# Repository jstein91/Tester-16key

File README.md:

# Tester 16key
 16 key Micropad design

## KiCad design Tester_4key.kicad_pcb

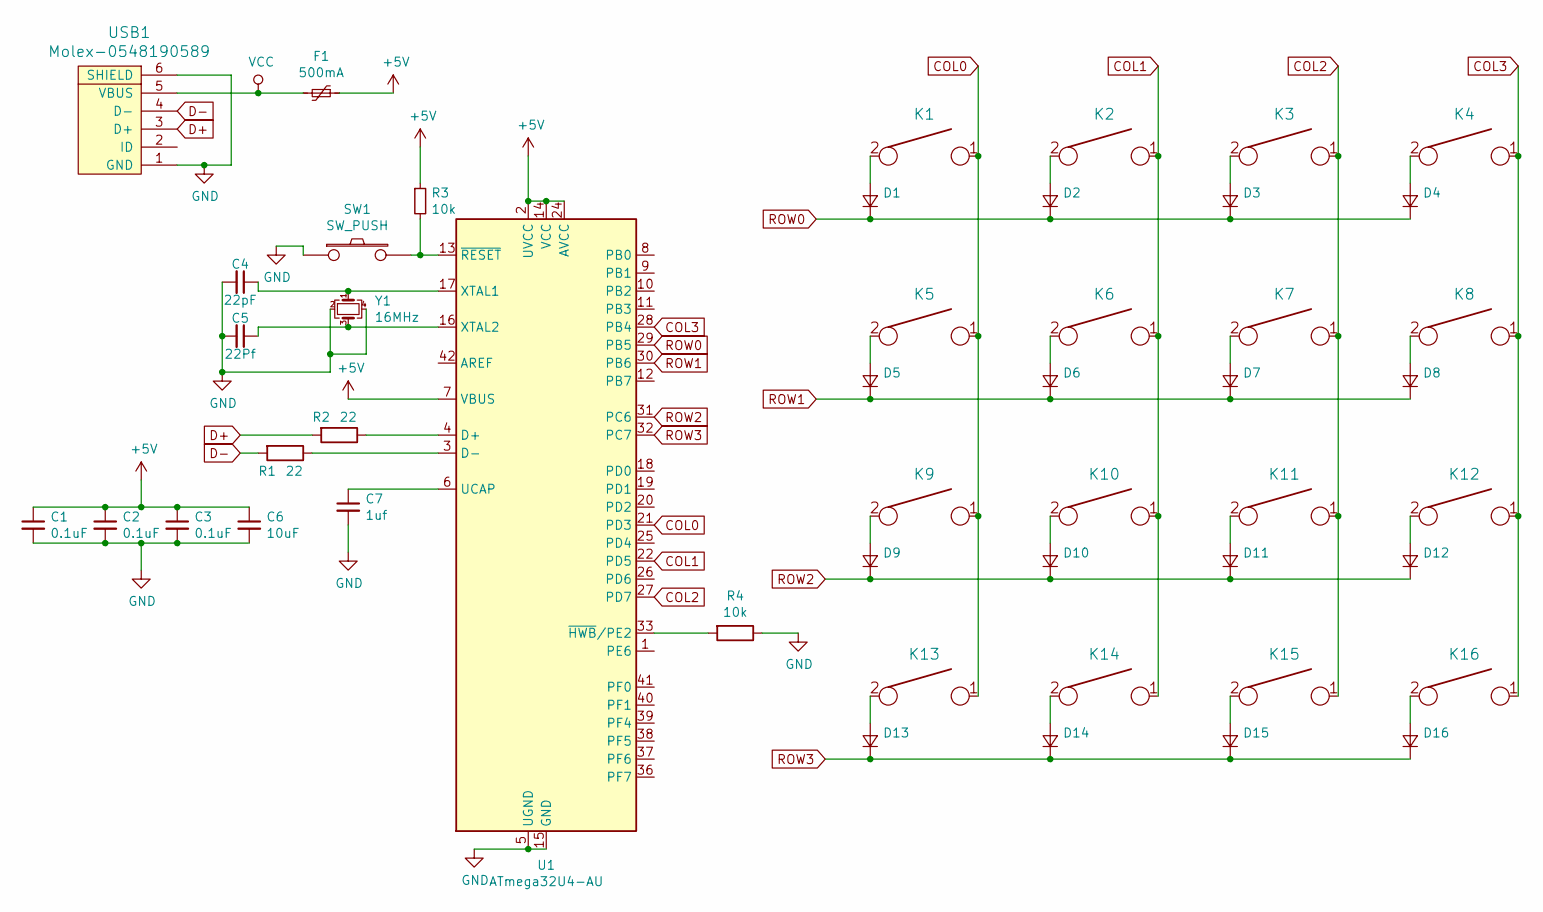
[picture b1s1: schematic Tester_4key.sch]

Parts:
C1, C2, C3: 0.1uF; C_0805_2012Metric_Pad1.15x1.40mm_HandSolder
C4: 22pF; C_0805_2012Metric_Pad1.15x1.40mm_HandSolder
C5: 22Pf; C_0805_2012Metric_Pad1.15x1.40mm_HandSolder
C6: 10uF; C_0805_2012Metric_Pad1.15x1.40mm_HandSolder
C7: 1uf; C_0805_2012Metric_Pad1.15x1.40mm_HandSolder
D1, D2, D3, D4, D5, D6, D7, D8, D9, D10, D11, D12, D13, D14, D15, D16: D_SOD123_axial
F1: 500mA; Fuse_1206_3216Metric_Pad1.42x1.75mm_HandSolder
K1, K2, K3, K4, K5, K6, K7, K8, K9, K10, K11, K12, K13, K14, K15, K16: KEYSW; Mx_Alps_100
R1, R2: 22; R_0805_2012Metric_Pad1.15x1.40mm_HandSolder
R3, R4: 10k; R_0805_2012Metric_Pad1.15x1.40mm_HandSolder
SW1: SW_PUSH; SKQG-1155865
U1: ATmega32U4-AU; TQFP-44_10x10mm_P0.8mm
USB1: Molex-0548190589
Y1: 16MHz; Crystal_SMD_3225-4Pin_3.2x2.5mm_HandSoldering

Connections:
+5V: C1.1, C2.1, C3.1, C6.1, F1.1, R3.1, U1.2 (UVCC), U1.7 (VBUS), U1.14 (VCC), U1.24 (AVCC), U1.34 (VCC), U1.44 (AVCC)
COL0: K1.1, K5.1, K9.1, K13.1, U1.21 (PD3)
COL1: K2.1, K6.1, K10.1, K14.1, U1.22 (PD5)
COL2: K3.1, K7.1, K11.1, K15.1, U1.27 (PD7)
COL3: K4.1, K8.1, K12.1, K16.1, U1.28 (PB4)
D+: R2.2, USB1.3 (D+)
D-: R1.2, USB1.4 (D-)
GND: C1.2, C2.2, C3.2, C4.2, C5.2, C6.2, C7.2, R4.1, SW1.1, U1.5 (UGND), U1.15 (GND), U1.23 (GND), U1.35 (GND), U1.43 (GND), USB1.1 (GND), USB1.6 (SHIELD), Y1.2, Y1.4
unnamed: C4.1, U1.17 (XTAL1), Y1.1
unnamed: C5.1, U1.16 (XTAL2), Y1.3
unnamed: C7.1, U1.6 (UCAP)
unnamed: D1.2 (A), K1.2
unnamed: D2.2 (A), K2.2
unnamed: D3.2 (A), K3.2
unnamed: D4.2 (A), K4.2
unnamed: D5.2 (A), K5.2
unnamed: D6.2 (A), K6.2
unnamed: D7.2 (A), K7.2
unnamed: D8.2 (A), K8.2
unnamed: D9.2 (A), K9.2
unnamed: D10.2 (A), K10.2
unnamed: D11.2 (A), K11.2
unnamed: D12.2 (A), K12.2
unnamed: D13.2 (A), K13.2
unnamed: D14.2 (A), K14.2
unnamed: D15.2 (A), K15.2
unnamed: D16.2 (A), K16.2
unnamed: R1.1, U1.3 (D-)
unnamed: R2.1, U1.4 (D+)
unnamed: R3.2, SW1.2, U1.13 (~RESET)
unnamed: R4.2, U1.33 (~HWB~/PE2)
ROW0: D1.1 (K), D2.1 (K), D3.1 (K), D4.1 (K), U1.29 (PB5)
ROW1: D5.1 (K), D6.1 (K), D7.1 (K), D8.1 (K), U1.30 (PB6)
ROW2: D9.1 (K), D10.1 (K), D11.1 (K), D12.1 (K), U1.31 (PC6)
ROW3: D13.1 (K), D14.1 (K), D15.1 (K), D16.1 (K), U1.32 (PC7)
VCC: F1.2, USB1.5 (VBUS)

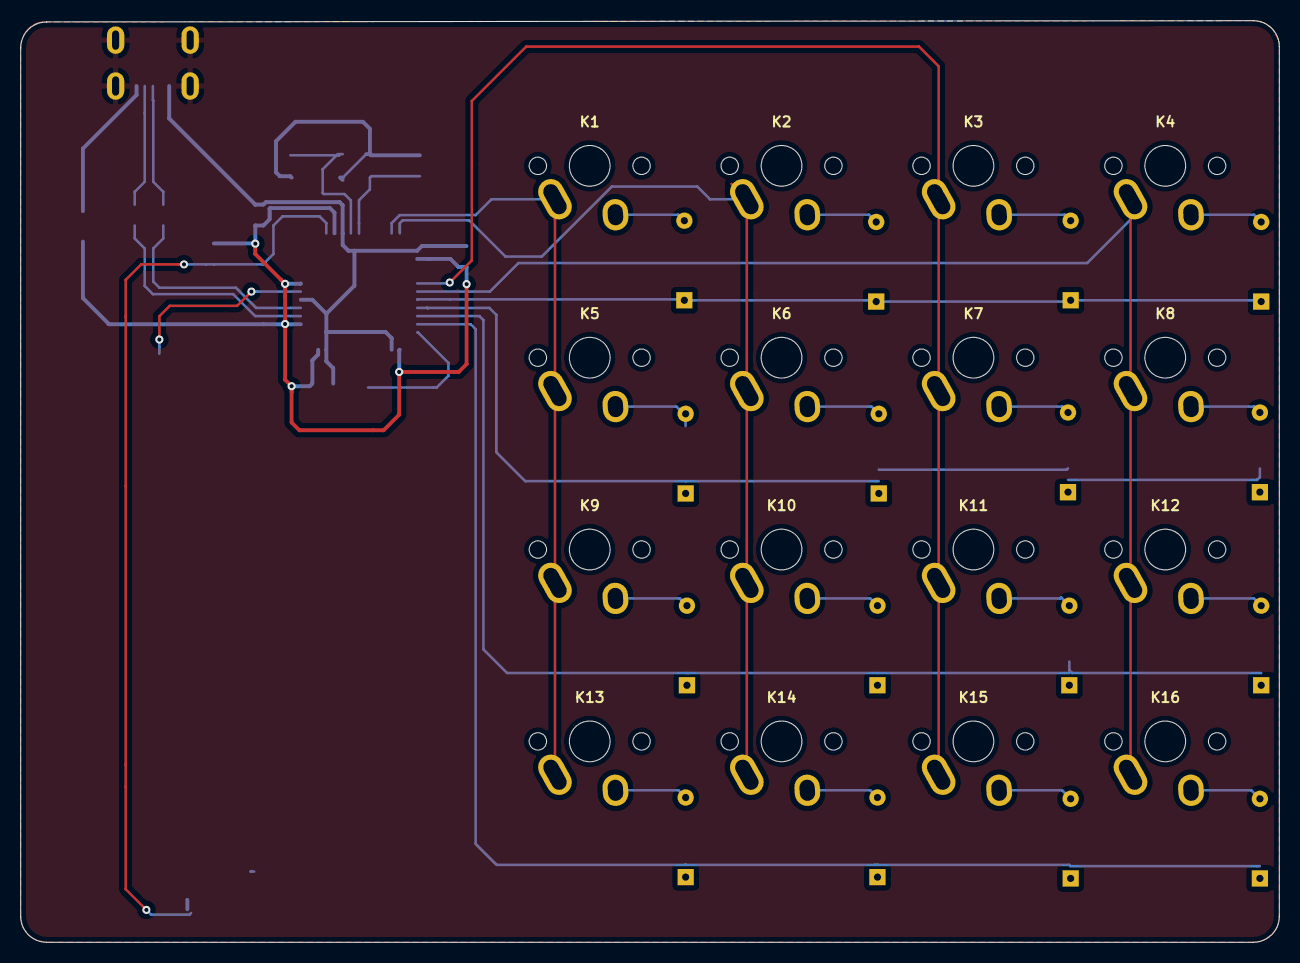
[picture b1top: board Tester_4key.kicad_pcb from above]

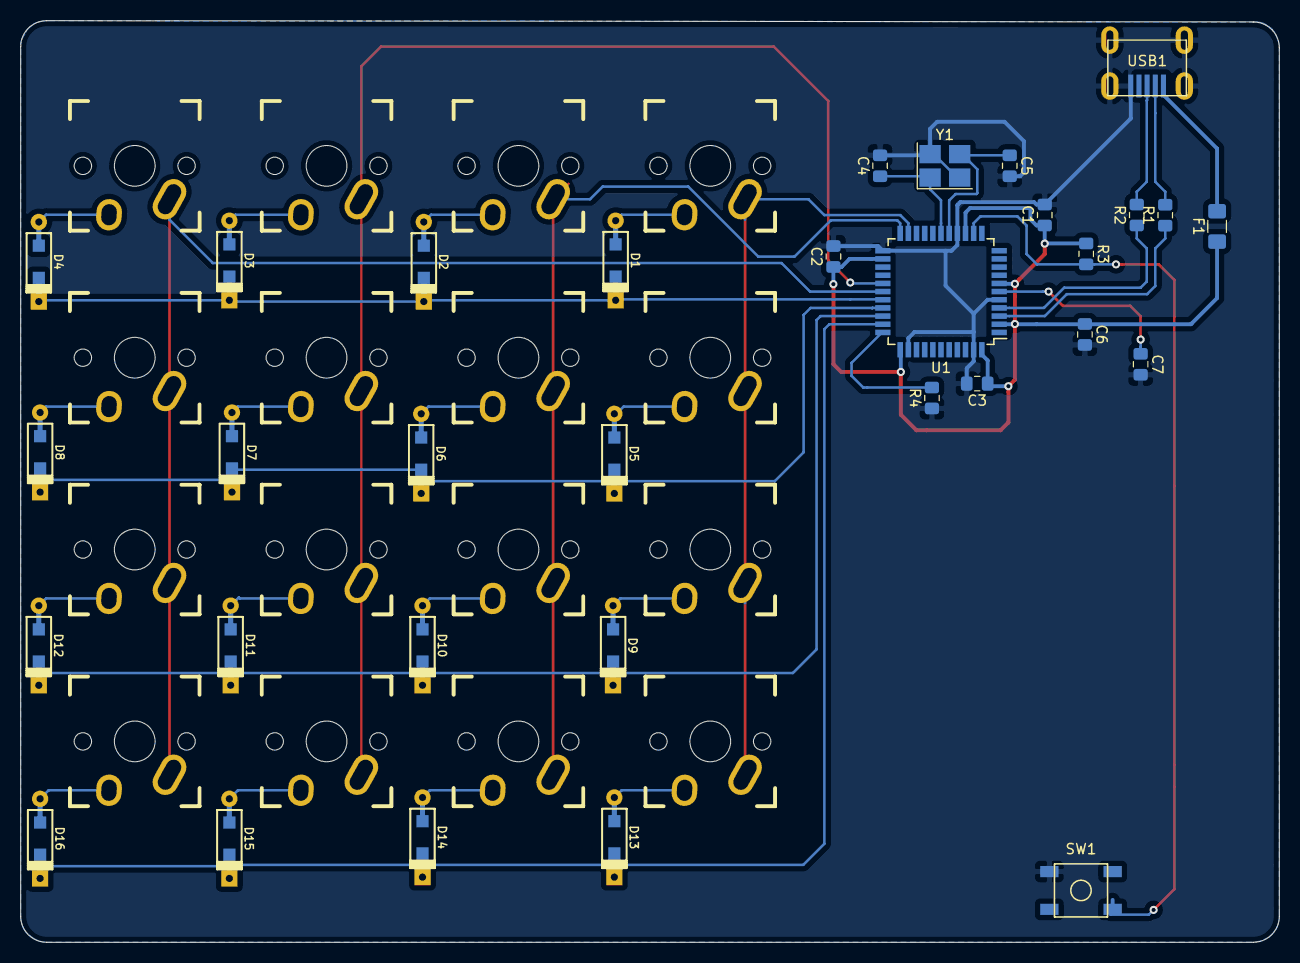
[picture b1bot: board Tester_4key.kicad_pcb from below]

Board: 2 copper layers, 123.3 x 90.3 mm, 48 parts (48 on the bottom side), 36 nets.

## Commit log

2019-08-02 initial upload
2019-08-02 Uplaod PDFs
2019-08-02 add mounting holes
2019-08-06 Tweaks
